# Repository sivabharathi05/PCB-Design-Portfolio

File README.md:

# PCB-Design-Portfolio
Collection of PCB design projects using KiCad .

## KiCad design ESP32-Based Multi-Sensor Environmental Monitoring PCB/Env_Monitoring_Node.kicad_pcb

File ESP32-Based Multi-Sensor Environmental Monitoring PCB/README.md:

# ESP32-Based Multi-Sensor Environmental Monitoring PCB

## 📌 Project Overview
This project is a custom-designed PCB using KiCad for an ESP32-based environmental monitoring system. The board integrates multiple sensors to measure real-time environmental parameters and display the data.

---

## 🎯 Objective
To design a compact and efficient PCB capable of:
- Interfacing multiple sensors
- Processing both analog and digital signals
- Displaying real-time data
- Serving as a base for IoT applications

---

## ⚙️ Components Used

### 🔹 Microcontroller
- ESP32-WROOM-32

### 🔹 Sensors
- BME280 (Temperature, Humidity, Pressure)
- MQ2 Gas Sensor (Air quality / Smoke detection)
- LDR (Light intensity measurement)

### 🔹 Display
- 0.91" OLED Display (I2C)

### 🔹 Passive Components
- Resistors (Voltage divider + Pull-ups)
- Capacitors (0.1µF, 10µF for decoupling)

---

## 🔌 System Architecture

Sensors → ESP32 → Data Processing → OLED Display

---

## 🔄 Working Principle

1. ESP32 reads sensor data:
   - BME280 via I2C communication
   - MQ2 and LDR via ADC pins
2. Data is processed inside the ESP32
3. Processed values are displayed on the OLED screen
4. The system can be extended for IoT cloud connectivity

---

## 🔗 Communication Protocol

### I2C Bus:
- SDA (Data)
- SCL (Clock)

Used for:
- BME280 Sensor
- OLED Display

Pull-up resistors (4.7kΩ) are used for stable communication.

---

## ⚡ Power Design

- Operates at 3.3V
- Decoupling capacitors:
  - 0.1µF → High-frequency noise filtering
  - 10µF → Voltage stabilization

---

## 🧠 Design Considerations

- Proper I2C routing
- Short signal paths
- Ground plane implementation
- Antenna keep-out area for ESP32
- Separation of analog and digital signals

---

## 🖥️ PCB Details

- 2-layer PCB
- Designed using KiCad
- Includes:
  - Schematic design
  - PCB layout
  - Gerber generation

---

## 📂 Files Included

- Schematic (.kicad_sch)
- PCB Layout (.kicad_pcb)
- Gerber Files (Manufacturing)
- 3D PCB Render Images

---

## 🚀 Future Improvements

- WiFi-based cloud data logging
- Mobile app integration
- Additional sensors integration

---

## 🛠️ Tools Used

- KiCad (EDA Tool)

---

## 💡 Note

This project is part of my self-learning journey in Embedded Systems and PCB Design.

---

## 📬 Contact

Open to feedback and collaboration opportunities in Embedded Systems and PCB Design.

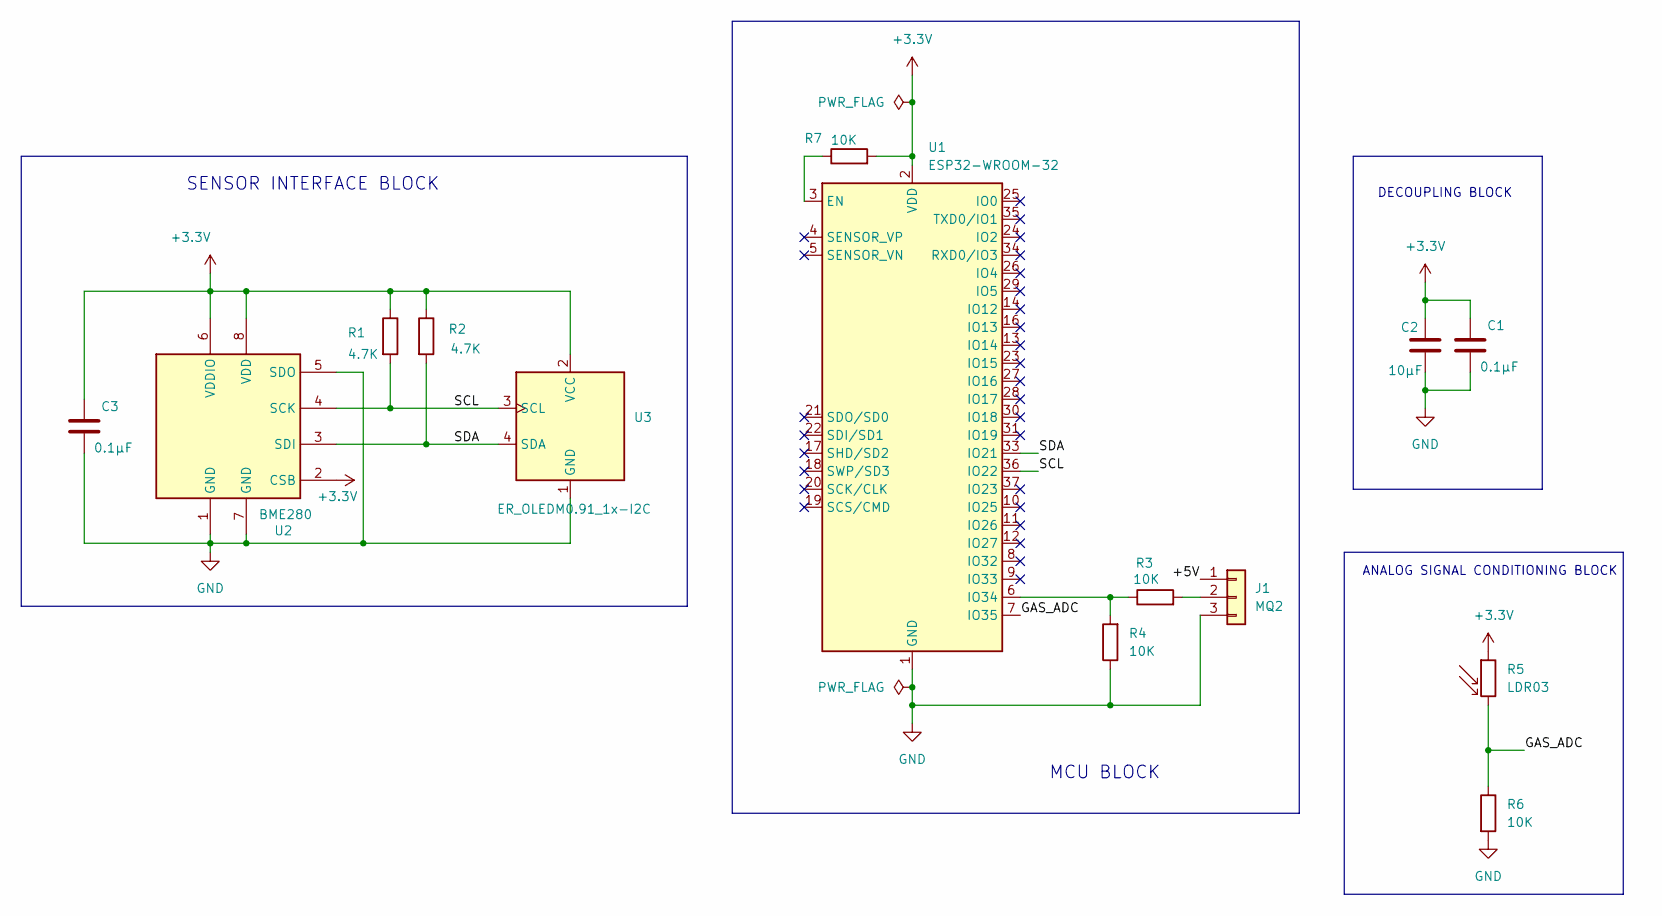
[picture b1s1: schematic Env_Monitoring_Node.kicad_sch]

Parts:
C1, C3: 0.1µF; C_0805_2012Metric
C2: 10µF; C_0805_2012Metric
J1: MQ2; PinHeader_1x03_P2.54mm_Vertical
R1, R2: 4.7K; R_0805_2012Metric
R3, R4, R6, R7: 10K; R_0805_2012Metric
R5: LDR03; R_LDR_10x8.5mm_P7.6mm_Vertical
U1: ESP32-WROOM-32
U2: BME280; Bosch_LGA-8_2.5x2.5mm_P0.65mm_ClockwisePinNumbering
U3: ER_OLEDM0.91_1x-I2C

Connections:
+3.3V: C1.1, C2.1, C3.1, R1.1, R2.1, R5.1, R7.2, U1.2 (VDD), U2.2 (CSB), U2.6 (VDDIO), U2.8 (VDD), U3.2 (VCC)
/+5V: J1.1
/GAS_ADC: R5.2, R6.1, U1.7 (IO35)
/SCL: R1.2, U1.36 (IO22), U2.4 (SCK), U3.3 (SCL)
/SDA: R2.2, U1.33 (IO21), U2.3 (SDI), U3.4 (SDA)
GND: C1.2, C2.2, C3.2, J1.3, R4.1, R6.2, U1.1 (GND), U1.15 (GND), U1.38 (GND), U1.39 (GND), U2.1 (GND), U2.5 (SDO), U2.7 (GND), U3.1 (GND)
unnamed: J1.2, R3.2
unnamed: R7.1, U1.3 (EN)
unnamed: R3.1, R4.2, U1.6 (IO34)

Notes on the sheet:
ANALOG SIGNAL CONDITIONING BLOCK
SENSOR INTERFACE BLOCK
DECOUPLING BLOCK
MCU BLOCK

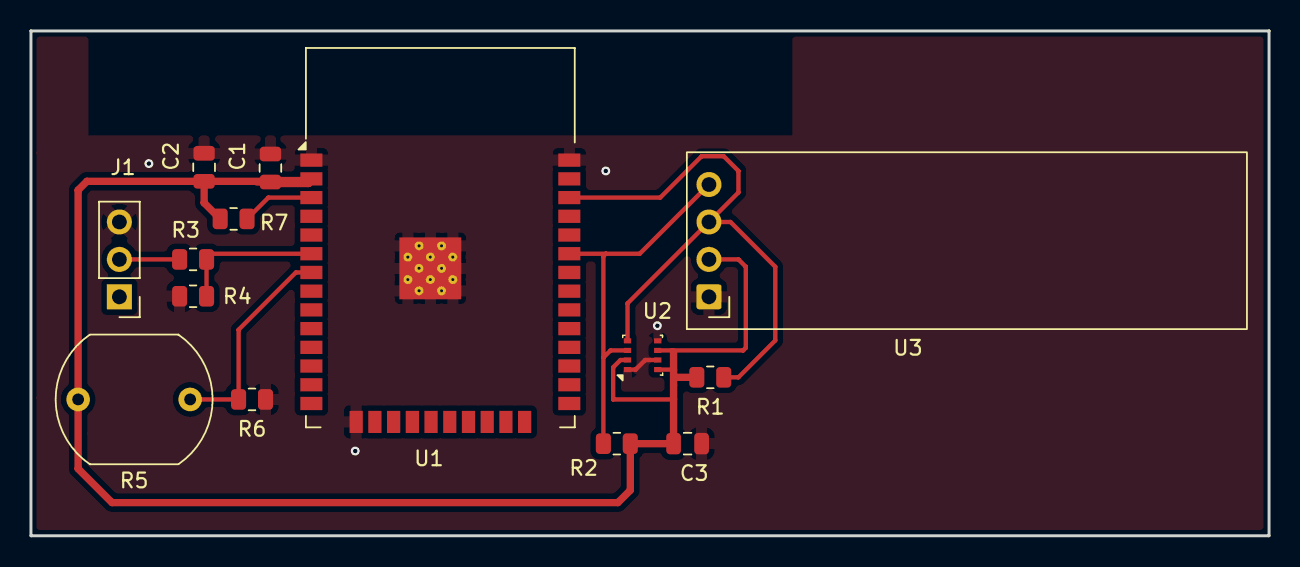
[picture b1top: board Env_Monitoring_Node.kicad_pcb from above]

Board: 2 copper layers, 84.0 x 34.2 mm, 14 parts (0 on the bottom side), 8 nets.

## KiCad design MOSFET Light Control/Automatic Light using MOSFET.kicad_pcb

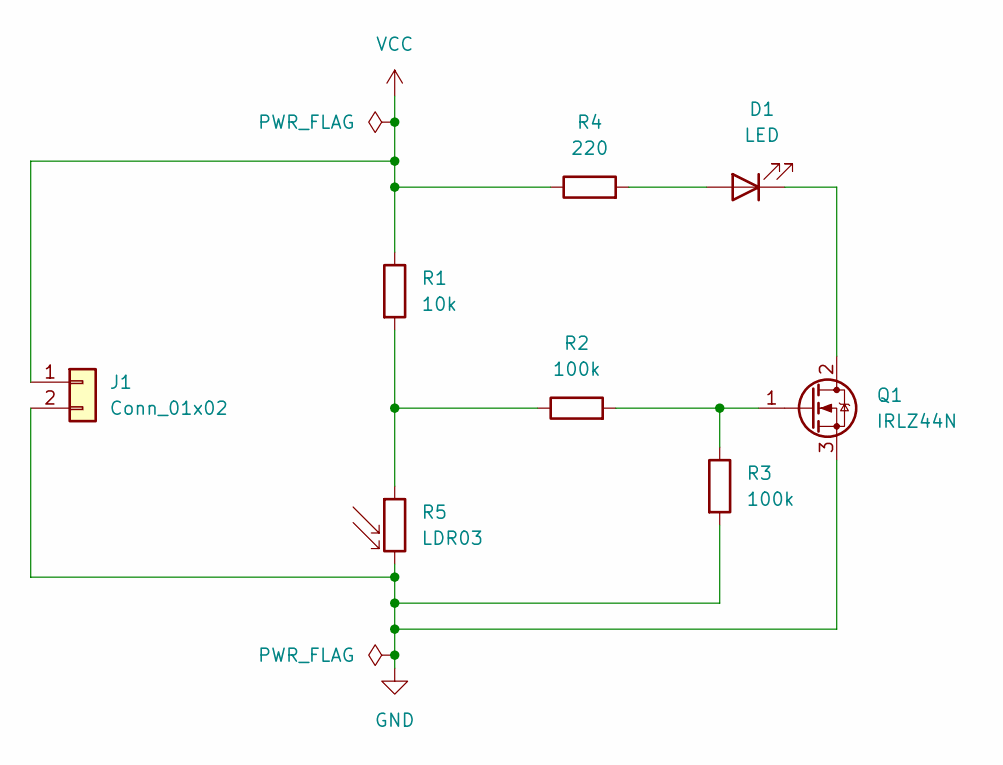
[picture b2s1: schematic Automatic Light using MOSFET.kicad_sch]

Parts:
D1: LED; LED_D5.0mm
J1: Conn_01x02; TerminalBlock_MaiXu_MX126-5.0-02P_1x02_P5.00mm
Q1: IRLZ44N; TO-220-3_Vertical
R1: 10k; R_Axial_DIN0207_L6.3mm_D2.5mm_P7.62mm_Horizontal
R2, R3: 100k; R_Axial_DIN0207_L6.3mm_D2.5mm_P7.62mm_Horizontal
R4: 220; R_Axial_DIN0207_L6.3mm_D2.5mm_P7.62mm_Horizontal
R5: LDR03; R_LDR_5.0x4.1mm_P3mm_Vertical

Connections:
GND: J1.2, Q1.3 (S), R3.2, R5.2
unnamed: D1.2 (A), R4.2
unnamed: D1.1 (K), Q1.2 (D)
unnamed: Q1.1 (G), R2.2, R3.1
unnamed: R1.2, R2.1, R5.1
VCC: J1.1, R1.1, R4.1

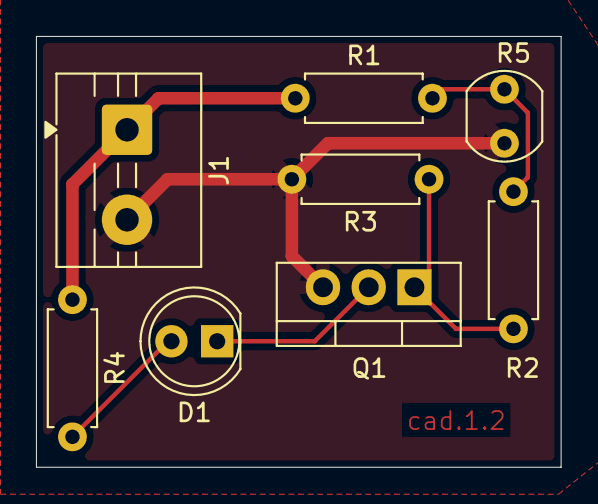
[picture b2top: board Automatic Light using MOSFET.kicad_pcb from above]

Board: 2 copper layers, 29.1 x 23.9 mm, 8 parts (0 on the bottom side), 6 nets.

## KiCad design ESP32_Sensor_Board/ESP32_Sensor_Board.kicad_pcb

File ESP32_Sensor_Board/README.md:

# ESP32-Based Multi-Sensor Environmental Monitoring PCB

## 📌 Project Overview
This project is a custom-designed PCB using KiCad for an ESP32-based environmental monitoring system. The board integrates multiple sensors to measure real-time environmental parameters and display the data.

## 🎯 Objective
To design a compact and efficient PCB capable of:
- Interfacing multiple sensors
- Processing both analog and digital signals
- Displaying real-time data
- Serving as a base for IoT applications

## ⚙️ Components Used

### 🔹 Microcontroller
- ESP32-WROOM-32

### 🔹 Sensors
- BME280 (Temperature, Humidity, Pressure)
- MQ2 Gas Sensor (Air quality / Smoke detection)
- LDR (Light intensity measurement)

### 🔹 Display
- 0.91" OLED Display (I2C)

### 🔹 Passive Components
- Resistors (Voltage divider + Pull-ups)
- Capacitors (0.1µF, 10µF for decoupling)

## 🔌 System Architecture

Sensors → ESP32 → Data Processing → OLED Display

## 🔄 Working Principle

1. ESP32 reads sensor data:
   - BME280 via I2C communication
   - MQ2 and LDR via ADC pins
2. Data is processed inside the ESP32
3. Processed values are displayed on the OLED screen
4. The system can be extended for IoT cloud connectivity

## 🔗 Communication Protocol

### I2C Bus:
- SDA (Data)
- SCL (Clock)

Used for:
- BME280 Sensor
- OLED Display

Pull-up resistors (4.7kΩ) are used for stable communication.

## ⚡ Power Design

- Operates at 3.3V
- Decoupling capacitors:
  - 0.1µF → High-frequency noise filtering
  - 10µF → Voltage stabilization

## 🧠 Design Considerations

- Proper I2C routing
- Short signal paths
- Ground plane implementation
- Antenna keep-out area for ESP32
- Separation of analog and digital signals

## 🖥️ PCB Details

- 2-layer PCB
- Designed using KiCad
- Includes:
  - Schematic design
  - PCB layout
  - Gerber generation

## 📂 Files Included

- Schematic (.kicad_sch)
- PCB Layout (.kicad_pcb)
- Gerber Files (Manufacturing)
- 3D PCB Render Images

## 🚀 Future Improvements

- WiFi-based cloud data logging
- Mobile app integration
- Additional sensors integration

## 🛠️ Tools Used

- KiCad (EDA Tool)

## 💡 Note

This project is part of my self-learning journey in Embedded Systems and PCB Design.

## 📬 Contact

Open to feedback and collaboration opportunities in Embedded Systems and PCB Design.

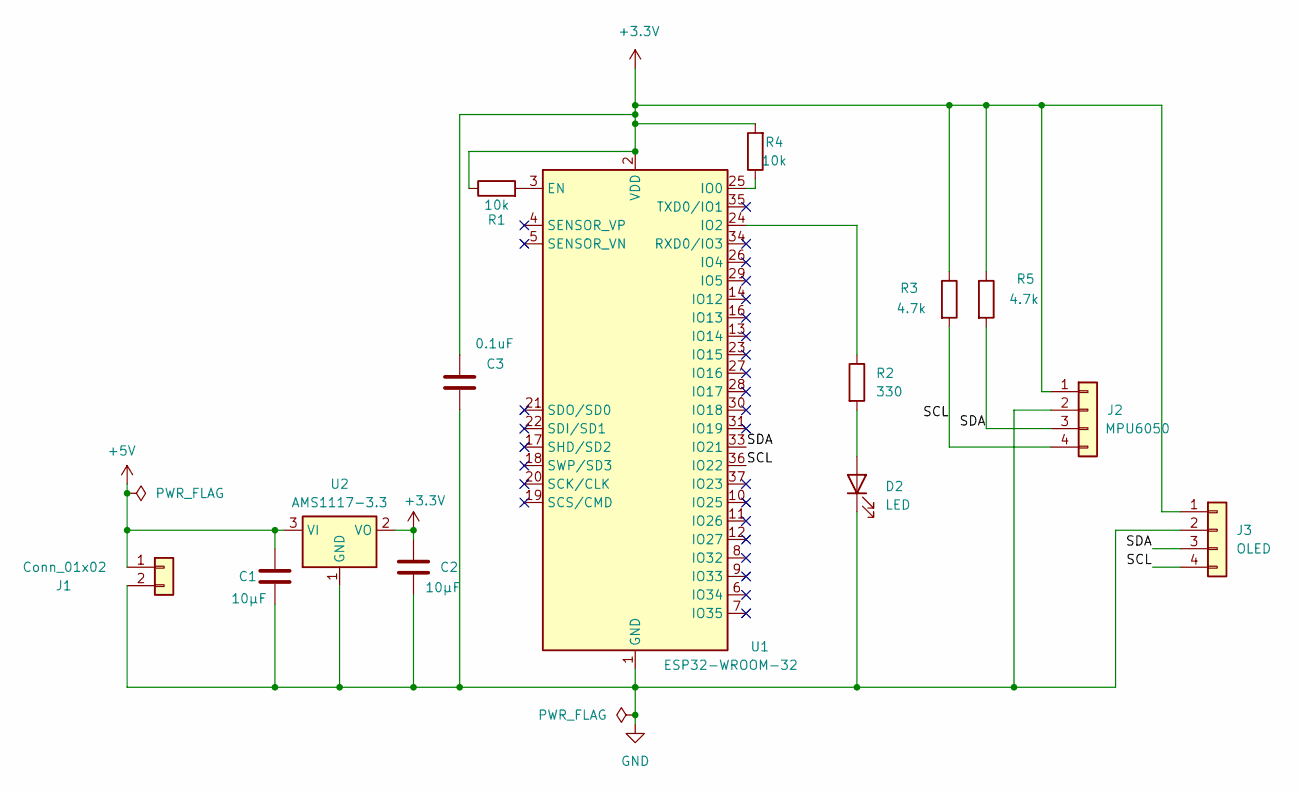
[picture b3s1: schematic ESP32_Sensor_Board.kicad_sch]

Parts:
C1, C2: 10µF; C_0805_2012Metric
C3: 0.1uF; C_0805_2012Metric
D2: LED; LED_0805_2012Metric
J1: Conn_01x02; PinHeader_1x02_P2.54mm_Vertical
J2: MPU6050; PinHeader_1x04_P2.54mm_Vertical
J3: OLED; PinHeader_1x04_P2.54mm_Vertical
R1, R4: 10k; R_0805_2012Metric
R2: 330; R_0805_2012Metric
R3, R5: 4.7k; R_0805_2012Metric
U1: ESP32-WROOM-32
U2: AMS1117-3.3; SOT-223-3_TabPin2

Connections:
+3.3V: C2.1, C3.1, J2.1, J3.1, R1.1, R3.1, R4.2, R5.1, U1.2 (VDD), U2.2 (VO)
+5V: C1.1, J1.1, U2.3 (VI)
/SCL: J2.4, J3.4, R3.2, U1.36 (IO22)
/SDA: J2.3, J3.3, R5.2, U1.33 (IO21)
GND: C1.2, C2.2, C3.2, D2.1 (K), J1.2, J2.2, J3.2, U1.1 (GND), U1.15 (GND), U1.38 (GND), U1.39 (GND), U2.1 (GND)
unnamed: D2.2 (A), R2.2
unnamed: R1.2, U1.3 (EN)
unnamed: R4.1, U1.25 (IO0)
unnamed: R2.1, U1.24 (IO2)

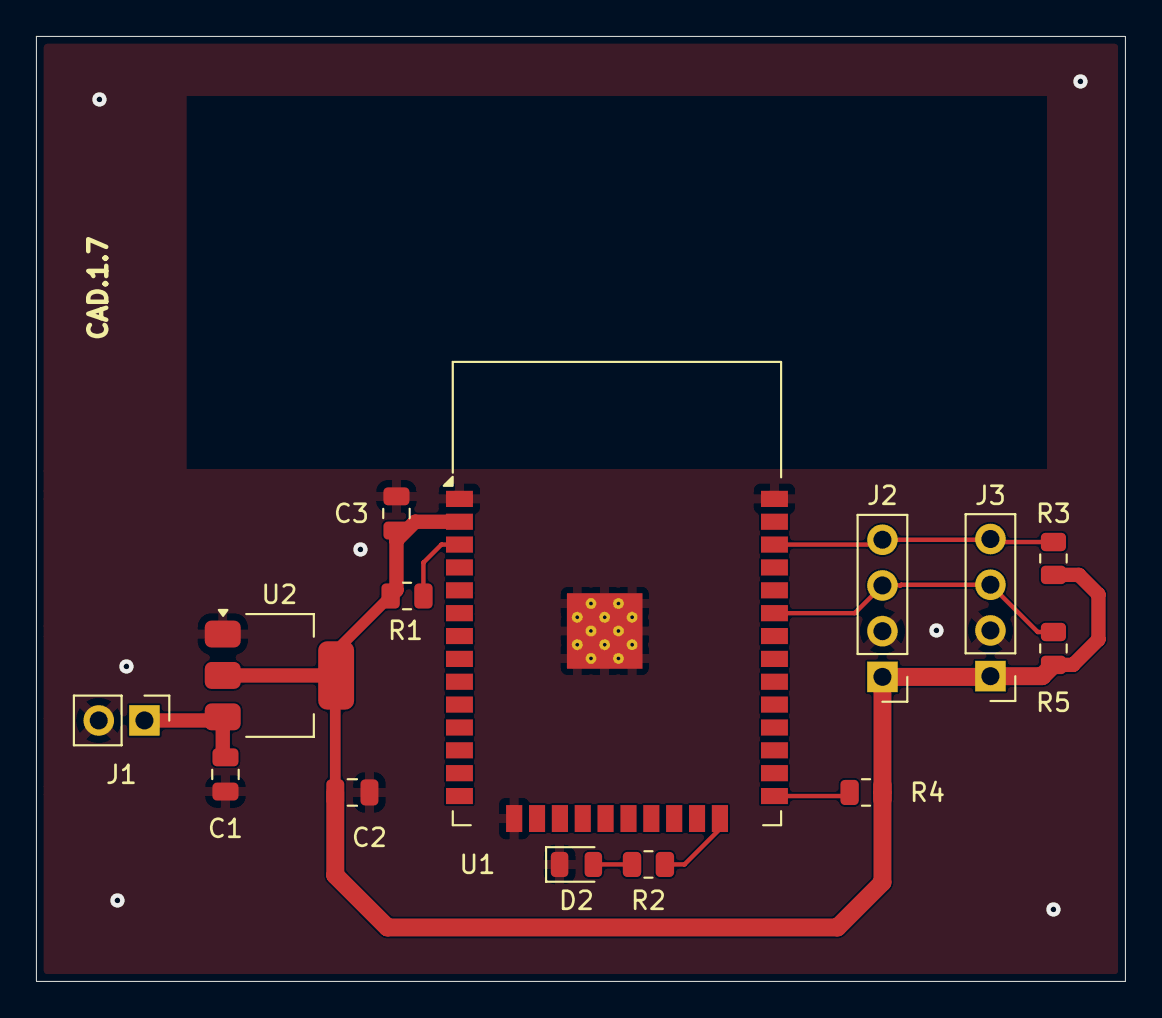
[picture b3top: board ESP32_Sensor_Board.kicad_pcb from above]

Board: 2 copper layers, 60.5 x 52.5 mm, 14 parts (0 on the bottom side), 9 nets.

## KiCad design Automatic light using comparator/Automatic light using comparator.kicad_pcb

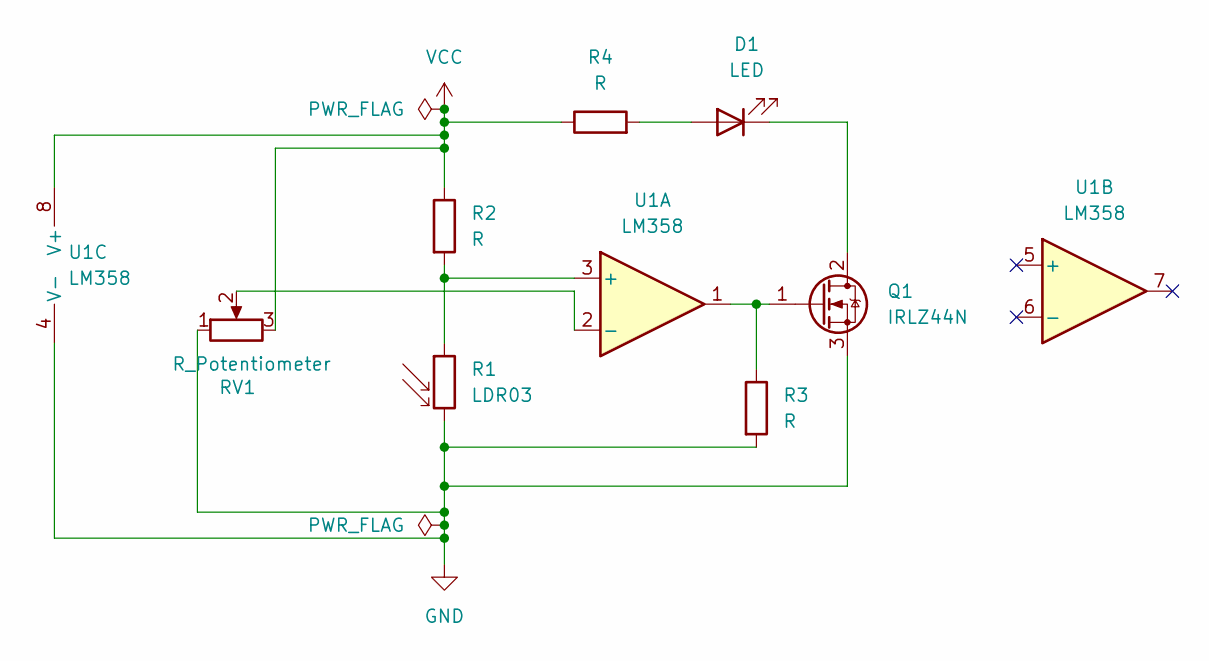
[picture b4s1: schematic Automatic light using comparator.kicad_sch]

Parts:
D1: LED; LED_D5.0mm
Q1: IRLZ44N; TO-220-3_Vertical
R1: LDR03; R_LDR_5.0x4.1mm_P3mm_Vertical
R2, R3, R4: R; R_Axial_DIN0207_L6.3mm_D2.5mm_P7.62mm_Horizontal
RV1: R_Potentiometer; Potentiometer_Bourns_3296P_Horizontal
U1: LM358; DIP-8_W7.62mm

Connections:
GND: Q1.3 (S), R1.2, R3.2, RV1.1, U1.4 (V-)
unnamed: D1.2 (A), R4.2
unnamed: D1.1 (K), Q1.2 (D)
unnamed: Q1.1 (G), R3.1, U1.1
unnamed: R1.1, R2.2, U1.3 (+)
unnamed: RV1.2, U1.2 (-)
VCC: R2.1, R4.1, RV1.3, U1.8 (V+)

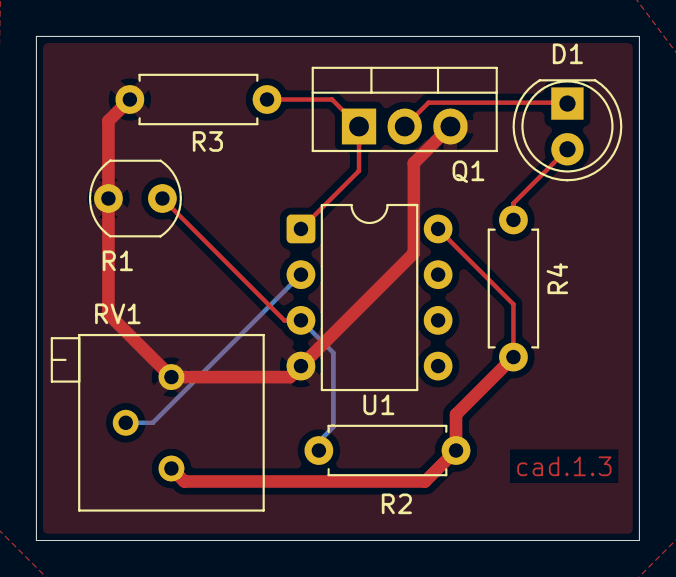
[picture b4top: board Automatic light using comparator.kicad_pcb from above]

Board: 2 copper layers, 33.5 x 28.0 mm, 8 parts (0 on the bottom side), 7 nets.

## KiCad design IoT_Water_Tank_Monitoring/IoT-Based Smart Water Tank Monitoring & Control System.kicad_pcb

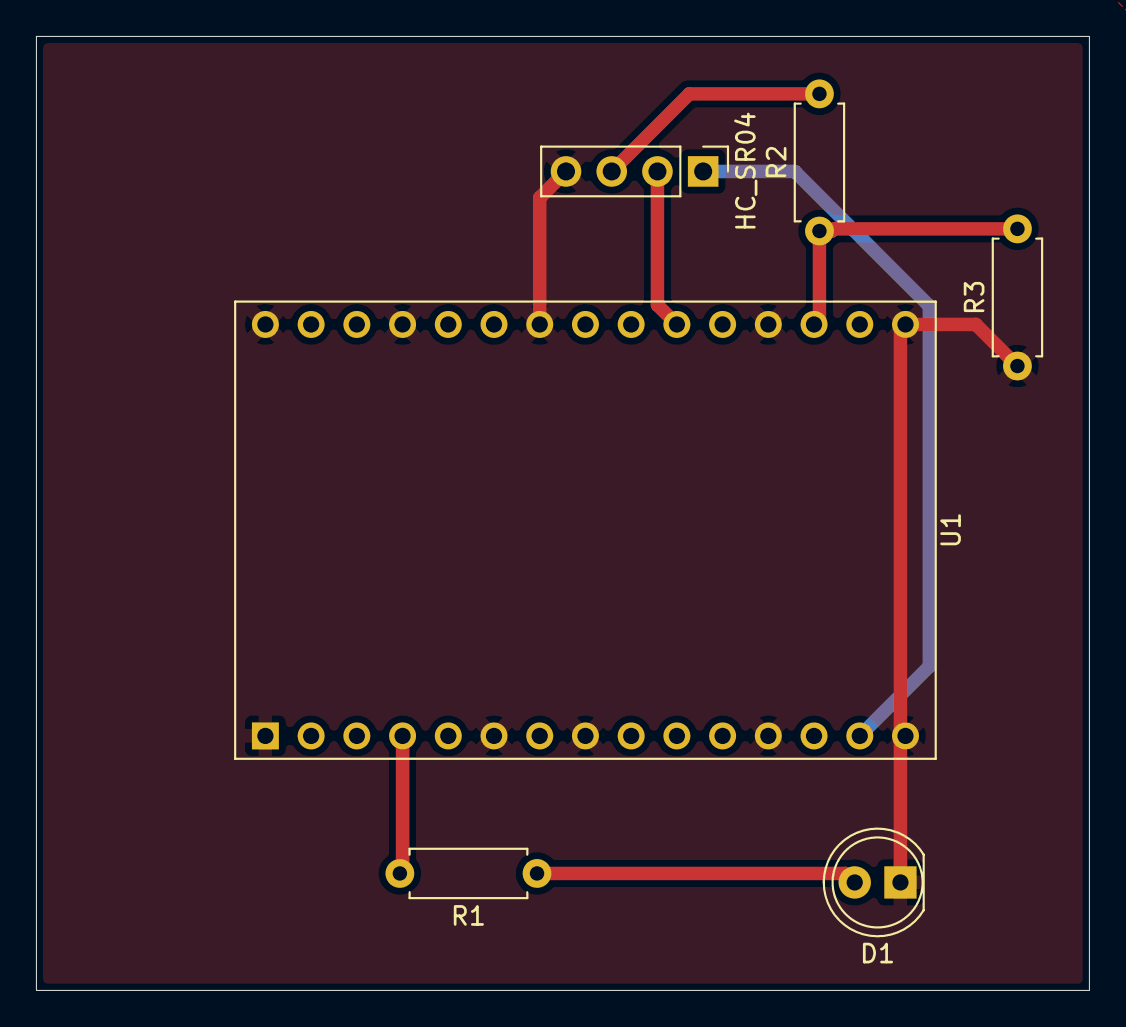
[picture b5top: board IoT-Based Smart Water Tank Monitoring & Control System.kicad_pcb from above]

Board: 2 copper layers, 58.5 x 53.0 mm, 6 parts (0 on the bottom side), 7 nets.

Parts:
D1: LED; LED_D5.0mm
HC_SR04: Conn_01x04; PinHeader_1x04_P2.54mm_Vertical
R1: 220; R_Axial_DIN0207_L6.3mm_D2.5mm_P7.62mm_Horizontal
R2: 1K; R_Axial_DIN0207_L6.3mm_D2.5mm_P7.62mm_Horizontal
R3: 2K; R_Axial_DIN0207_L6.3mm_D2.5mm_P7.62mm_Horizontal
U1: ESP32-C3-DevKitM-1

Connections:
+5V: HC_SR04.1 (VCC), U1.13 (5V), U1.14 (5V)
GND: D1.1 (K), HC_SR04.4 (GND), R3.1, U1.1 (GND), U1.6 (GND), U1.8 (GND), U1.12 (GND), U1.15 (GND), U1.16 (GND), U1.19 (GND), U1.24 (GND), U1.27 (GND), U1.30 (GND)
unnamed: D1.2 (A), R1.1
unnamed: HC_SR04.3 (ECHO), R2.2
unnamed: HC_SR04.2 (TRIG), U1.21 (IO5)
unnamed: R1.2, U1.4 (IO2)
unnamed: R2.1, R3.2, U1.18 (IO18)

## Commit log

2026-04-21 Add files via upload
    Added Automatic Light Comparator PCB project
2026-04-21 ESP32 Sensor Board
2026-04-21 IoT Water Tank Monitoring
2026-04-21 Create IoT_Water_Tank_Monitoring
2026-04-21 IoT_Water_Tank_Monitoring
2026-04-21 MOSFET Light Control
2026-04-29 ESP32 Sensor Board project
    ESP32 Sensor Board project
2026-04-29 ESP32-Based Multi-Sensor Environmental Monitoring
    ESP32-Based Multi-Sensor Environmental Monitoring
2026-04-29 Add design files and Gerber outputs
2026-04-29 3D view
